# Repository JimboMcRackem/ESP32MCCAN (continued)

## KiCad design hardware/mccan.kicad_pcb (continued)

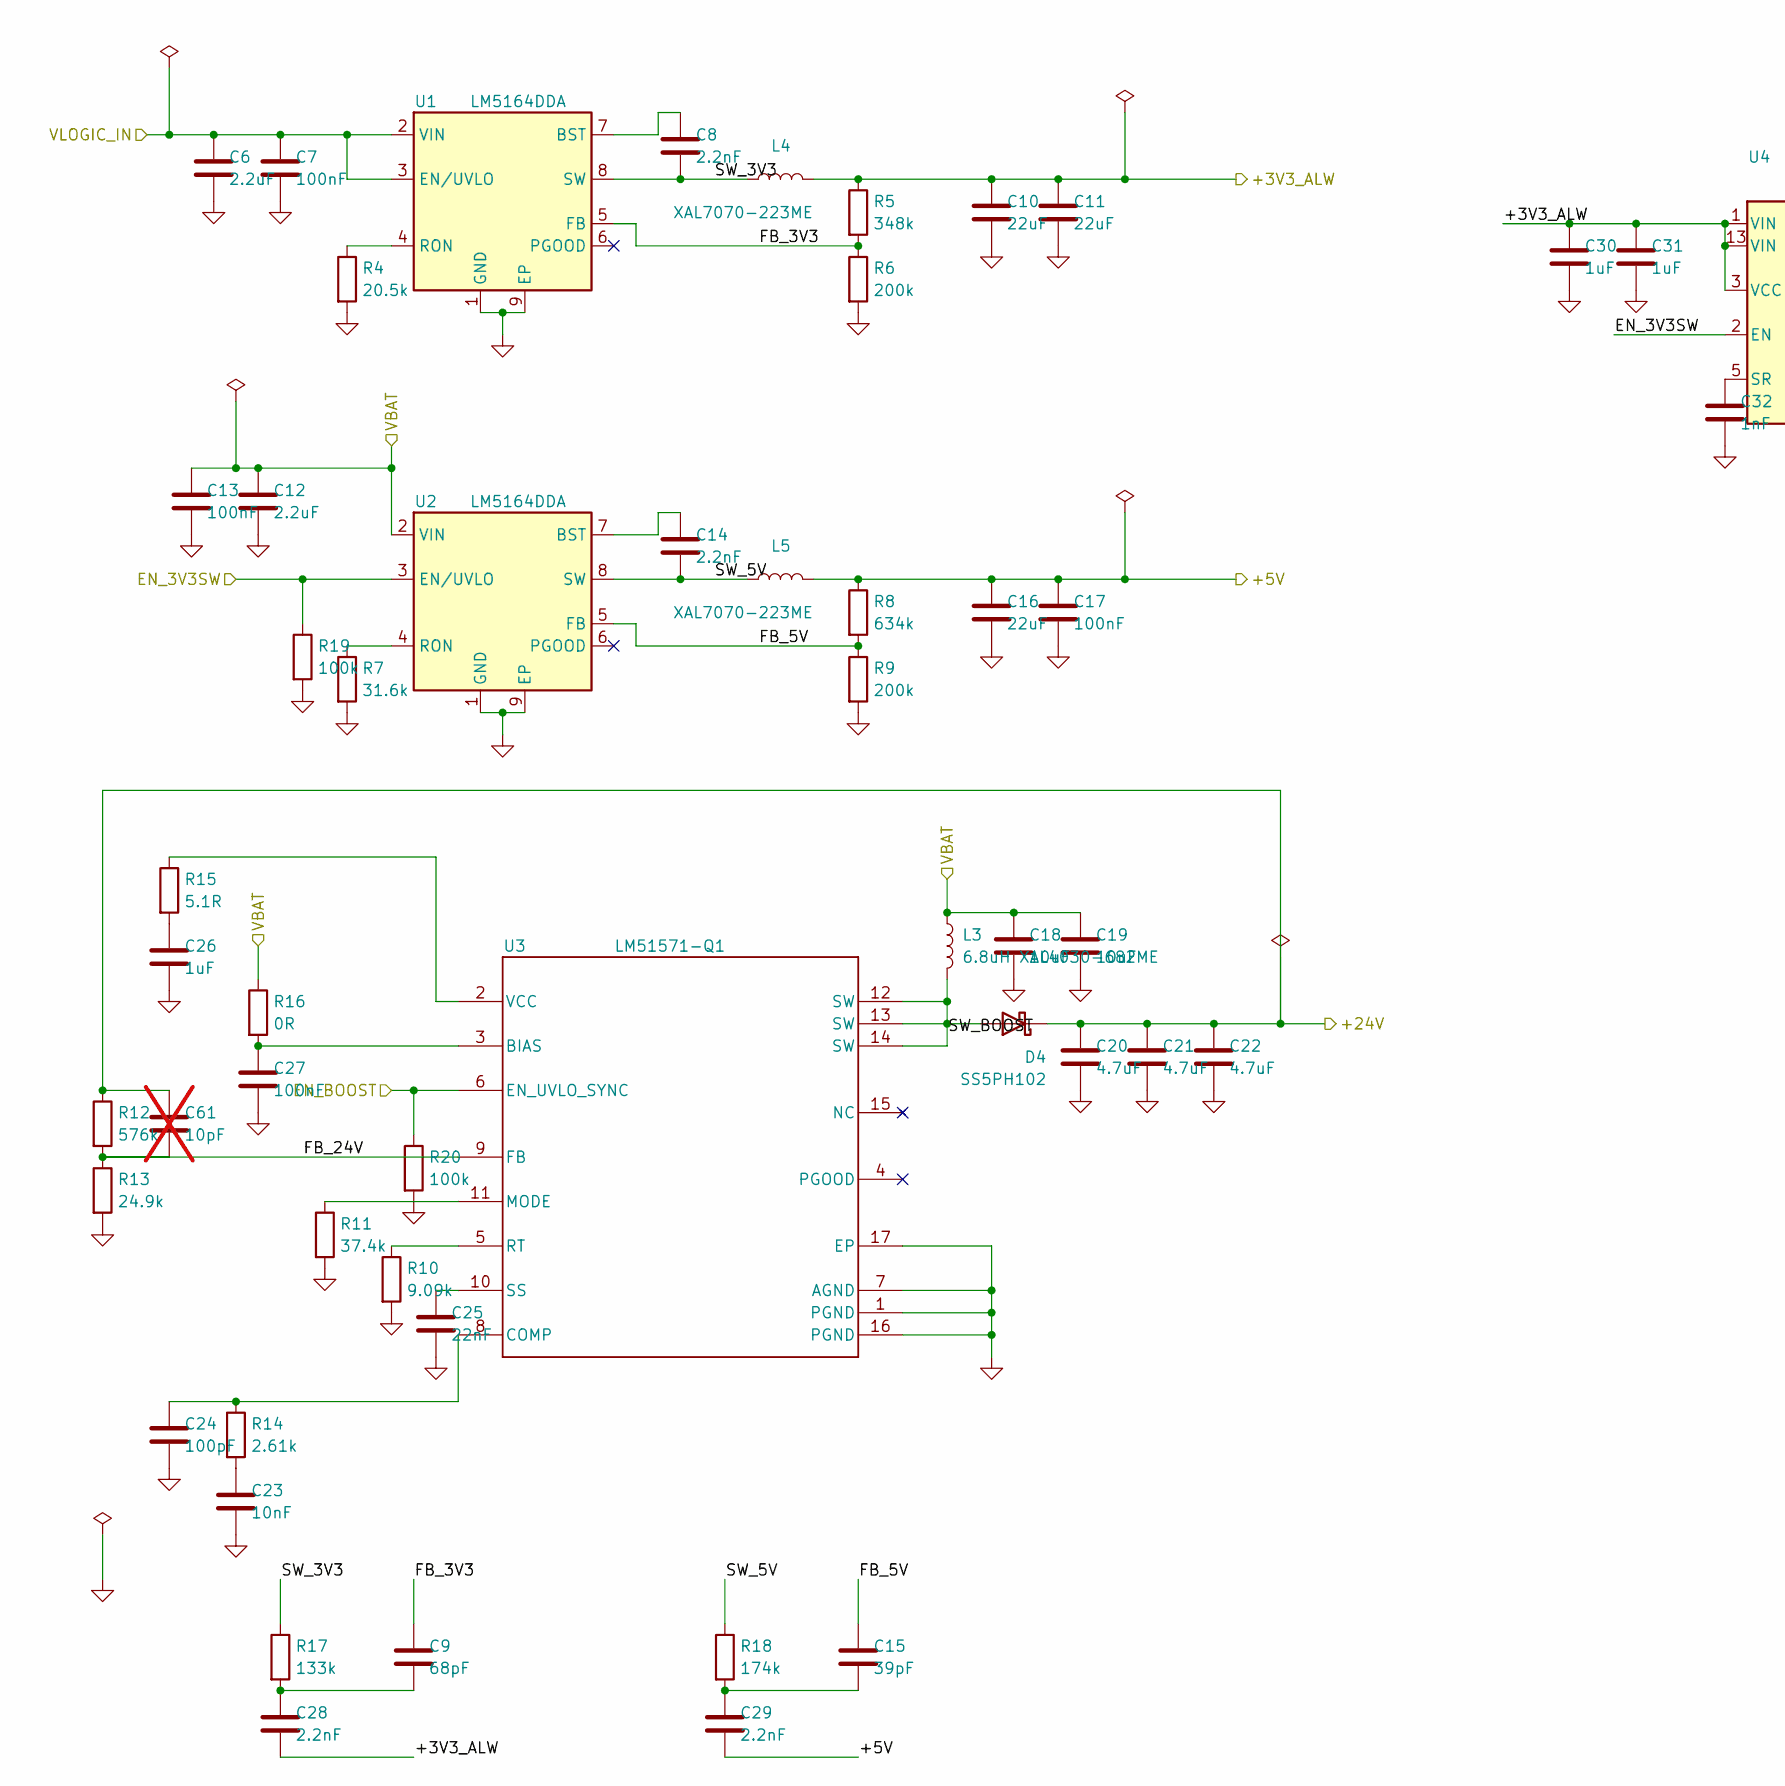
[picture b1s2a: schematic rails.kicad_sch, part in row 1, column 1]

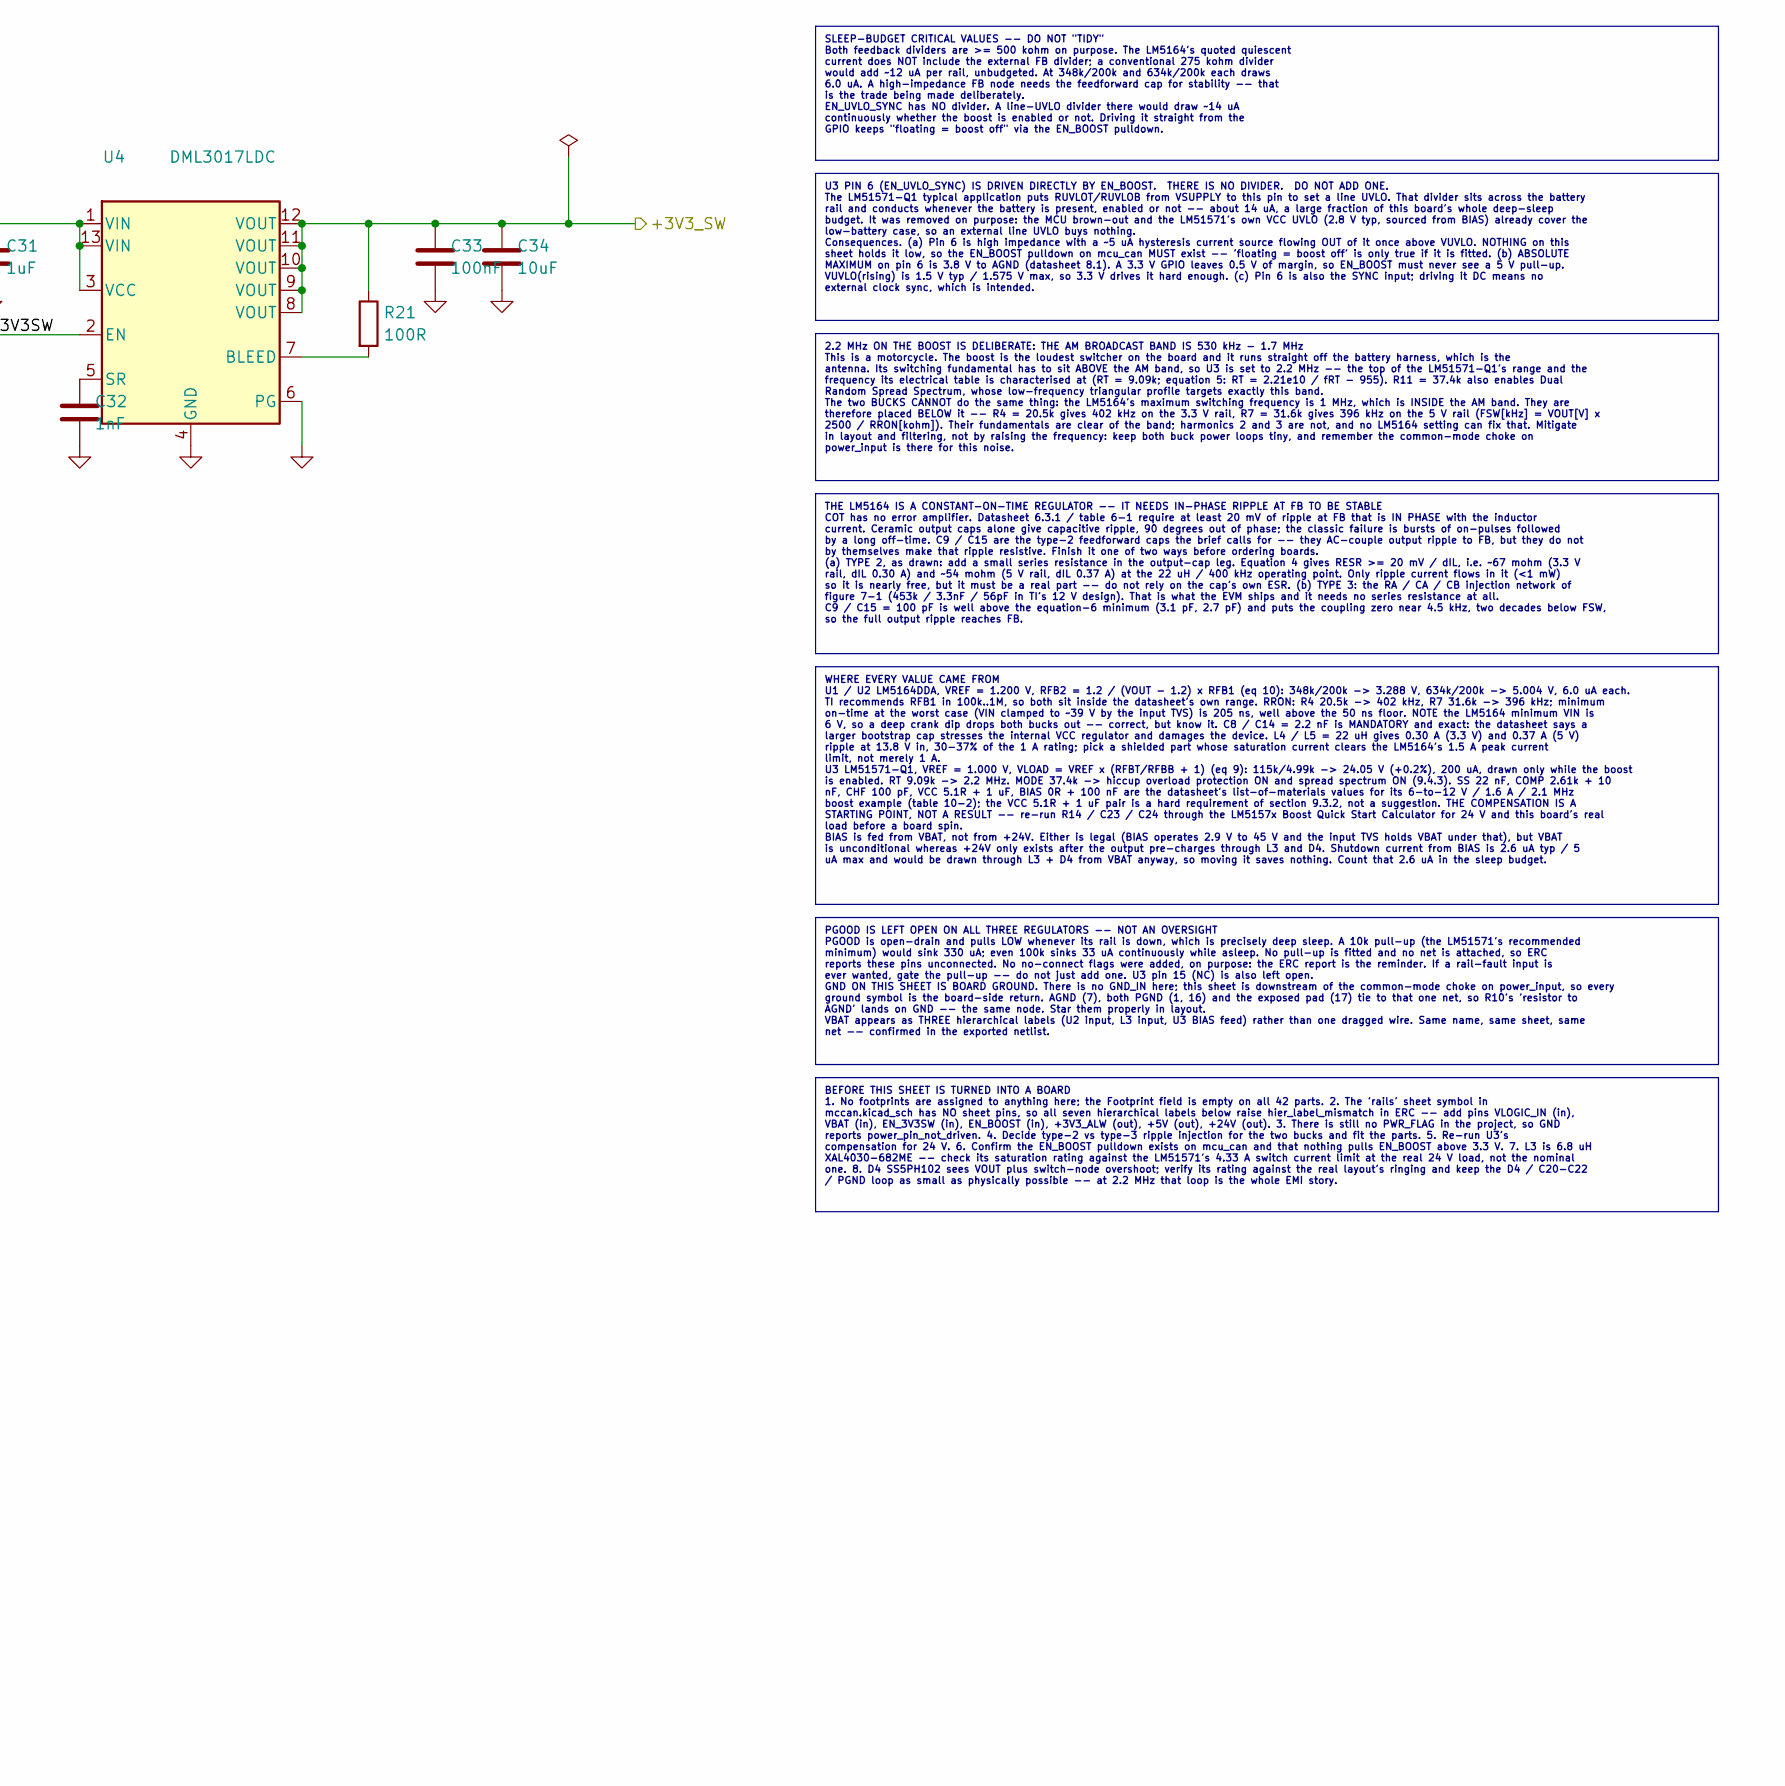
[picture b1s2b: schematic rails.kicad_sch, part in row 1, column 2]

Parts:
C6, C12: 2.2uF; C_1206_3216Metric
C7, C13: 100nF; C_0805_2012Metric
C8, C14, C28, C29: 2.2nF; C_0603_1608Metric
C9: 68pF; C_0603_1608Metric
C10, C11, C16: 22uF; C_0603_1608Metric
C15: 39pF; C_0603_1608Metric
C17, C27, C33: 100nF; C_0603_1608Metric
C18, C19: 10uF; C_1210_3225Metric
C20, C21, C22: 4.7uF; C_1206_3216Metric
C23: 10nF; C_0603_1608Metric
C24: 100pF; C_0603_1608Metric
C25: 22nF; C_0603_1608Metric
C26, C30, C31: 1uF; C_0603_1608Metric
C32: 1nF; C_0603_1608Metric
C34: 10uF; C_0603_1608Metric
C61: 10pF; C_0603_1608Metric; not fitted
D4: SS5PH102; TO-277A
L3: 6.8uH XAL4030-682ME; L_Coilcraft_XAL4030-XXX
L4, L5: XAL7070-223ME; L_Coilcraft_XAL7070-XXX
R4: 20.5k; R_0603_1608Metric
R5: 348k; R_0603_1608Metric
R6, R9: 200k; R_0603_1608Metric
R7: 31.6k; R_0603_1608Metric
R8: 634k; R_0603_1608Metric
R10: 9.09k; R_0603_1608Metric
R11: 37.4k; R_0603_1608Metric
R12: 576k; R_0603_1608Metric
R13: 24.9k; R_0603_1608Metric
R14: 2.61k; R_0603_1608Metric
R15: 5.1R; R_0603_1608Metric
R16: 0R; R_0603_1608Metric
R17: 133k; R_0603_1608Metric
R18: 174k; R_0603_1608Metric
R19, R20: 100k; R_0603_1608Metric
R21: 100R; R_0603_1608Metric
U1, U2: LM5164DDA; SOIC-8-1EP_3.9x4.9mm_P1.27mm_EP2.62x3.51mm
U3: LM51571-Q1; QFN-16-1EP_3x3mm_P0.5mm_EP1.675x1.675mm
U4: DML3017LDC; DFN-12-1EP_3x3mm_P0.5mm_EP2.05x2.86mm

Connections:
/+3V3_ALW: C10.1, C11.1, C28.2, C30.1, C31.1, L4.2, R5.1, U4.1 (VIN), U4.3 (VCC), U4.13 (VIN); also elsewhere on the board
/+3V3_SW: C33.1, C34.1, R21.1, U4.8 (VOUT), U4.9 (VOUT), U4.10 (VOUT), U4.11 (VOUT), U4.12 (VOUT); also elsewhere on the board
/+5V: C16.1, C17.1, C29.2, L5.2, R8.1; also elsewhere on the board
/+24V: C20.1, C21.1, C22.1, C61.1, D4.1 (K), D4.3 (K), R12.1; also elsewhere on the board
/EN_3V3SW: R19.1, U2.3 (EN/UVLO), U4.2 (EN); also elsewhere on the board
/EN_BOOST: R20.1, U3.6 (EN_UVLO_SYNC); also elsewhere on the board
/VBAT: C12.1, C13.1, C18.1, C19.1, L3.1, R16.1, U2.2 (VIN); also elsewhere on the board
/VLOGIC_IN: C6.1, C7.1, U1.2 (VIN), U1.3 (EN/UVLO); also elsewhere on the board
/rails/FB_3V3: C9.1, R5.2, R6.1, U1.5 (FB)
/rails/FB_5V: C15.1, R8.2, R9.1, U2.5 (FB)
/rails/FB_24V: C61.2, R12.2, R13.1, U3.9 (FB)
/rails/SW_3V3: C8.2, L4.1, R17.1, U1.8 (SW)
/rails/SW_5V: C14.2, L5.1, R18.1, U2.8 (SW)
/rails/SW_BOOST: D4.2 (A), L3.2, U3.12 (SW), U3.13 (SW), U3.14 (SW)
unnamed: C15.2, C29.1, R18.2
unnamed: C23.1, R14.2
unnamed: C26.1, R15.2
unnamed: C9.2, C28.1, R17.2
unnamed: C8.1, U1.7 (BST)
unnamed: R4.1, U1.4 (RON)
unnamed: C14.1, U2.7 (BST)
unnamed: R7.1, U2.4 (RON)
unnamed: C27.1, R16.2, U3.3 (BIAS)
unnamed: C24.1, R14.1, U3.8 (COMP)
unnamed: R10.1, U3.5 (RT)
unnamed: C25.1, U3.10 (SS)
unnamed: R15.1, U3.2 (VCC)
unnamed: R21.2, U4.7 (BLEED)
unnamed: C32.1, U4.5 (SR)

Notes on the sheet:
PGOOD IS LEFT OPEN ON ALL THREE REGULATORS -- NOT AN OVERSIGHT PGOOD is open-drain and pulls LOW whenever its rail is down, which is precisely deep sleep. A 10k pull-up (the LM51571's recommended minimum) would sink 330 uA; even 100k sinks 33 uA continuously while asleep. No pull-up is fitted and n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
2.2 MHz ON THE BOOST IS DELIBERATE: THE AM BROADCAST BAND IS 530 kHz - 1.7 MHz This is a motorcycle. The boost is the loudest switcher on the board and it runs straight off the battery harness, which is the antenna. Its switching fundamental has to sit ABOVE the AM band, so U3 is set to 2.2 MHz -- 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
BEFORE THIS SHEET IS TURNED INTO A BOARD 1. No footprints are assigned to anything here; the Footprint field is empty on all 42 parts. 2. The 'rails' sheet symbol in mccan.kicad_sch has NO sheet pins, so all seven hierarchical labels below raise hier_label_mismatch in ERC -- add pins VLOGIC_IN (in)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
WHERE EVERY VALUE CAME FROM U1 / U2 LM5164DDA, VREF = 1.200 V, RFB2 = 1.2 / (VOUT - 1.2) x RFB1 (eq 10): 348k/200k -> 3.288 V, 634k/200k -> 5.004 V, 6.0 uA each. TI recommends RFB1 in 100k..1M, so both sit inside the datasheet's own range. RRON: R4 20.5k -> 402 kHz, R7 31.6k -> 396 kHz; minimum on-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
THE LM5164 IS A CONSTANT-ON-TIME REGULATOR -- IT NEEDS IN-PHASE RIPPLE AT FB TO BE STABLE COT has no error amplifier. Datasheet 6.3.1 / table 6-1 require at least 20 mV of ripple at FB that is IN PHASE with the inductor current. Ceramic output caps alone give capacitive ripple, 90 degrees out of ph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
SLEEP-BUDGET CRITICAL VALUES -- DO NOT "TIDY" Both feedback dividers are >= 500 kohm on purpose. The LM5164's quoted quiescent current does NOT include the external FB divider; a conventional 275 kohm divider would add ~12 uA per rail, unbudgeted. At 348k/200k and 634k/200k each draws 6.0 uA. A hig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
U3 PIN 6 (EN_UVLO_SYNC) IS DRIVEN DIRECTLY BY EN_BOOST. THERE IS NO DIVIDER. DO NOT ADD ONE. The LM51571-Q1 typical application puts RUVLOT/RUVLOB from VSUPPLY to this pin to set a line UVLO. That divider sits across the battery rail and conducts whenever the battery is present, enabled or not -- a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

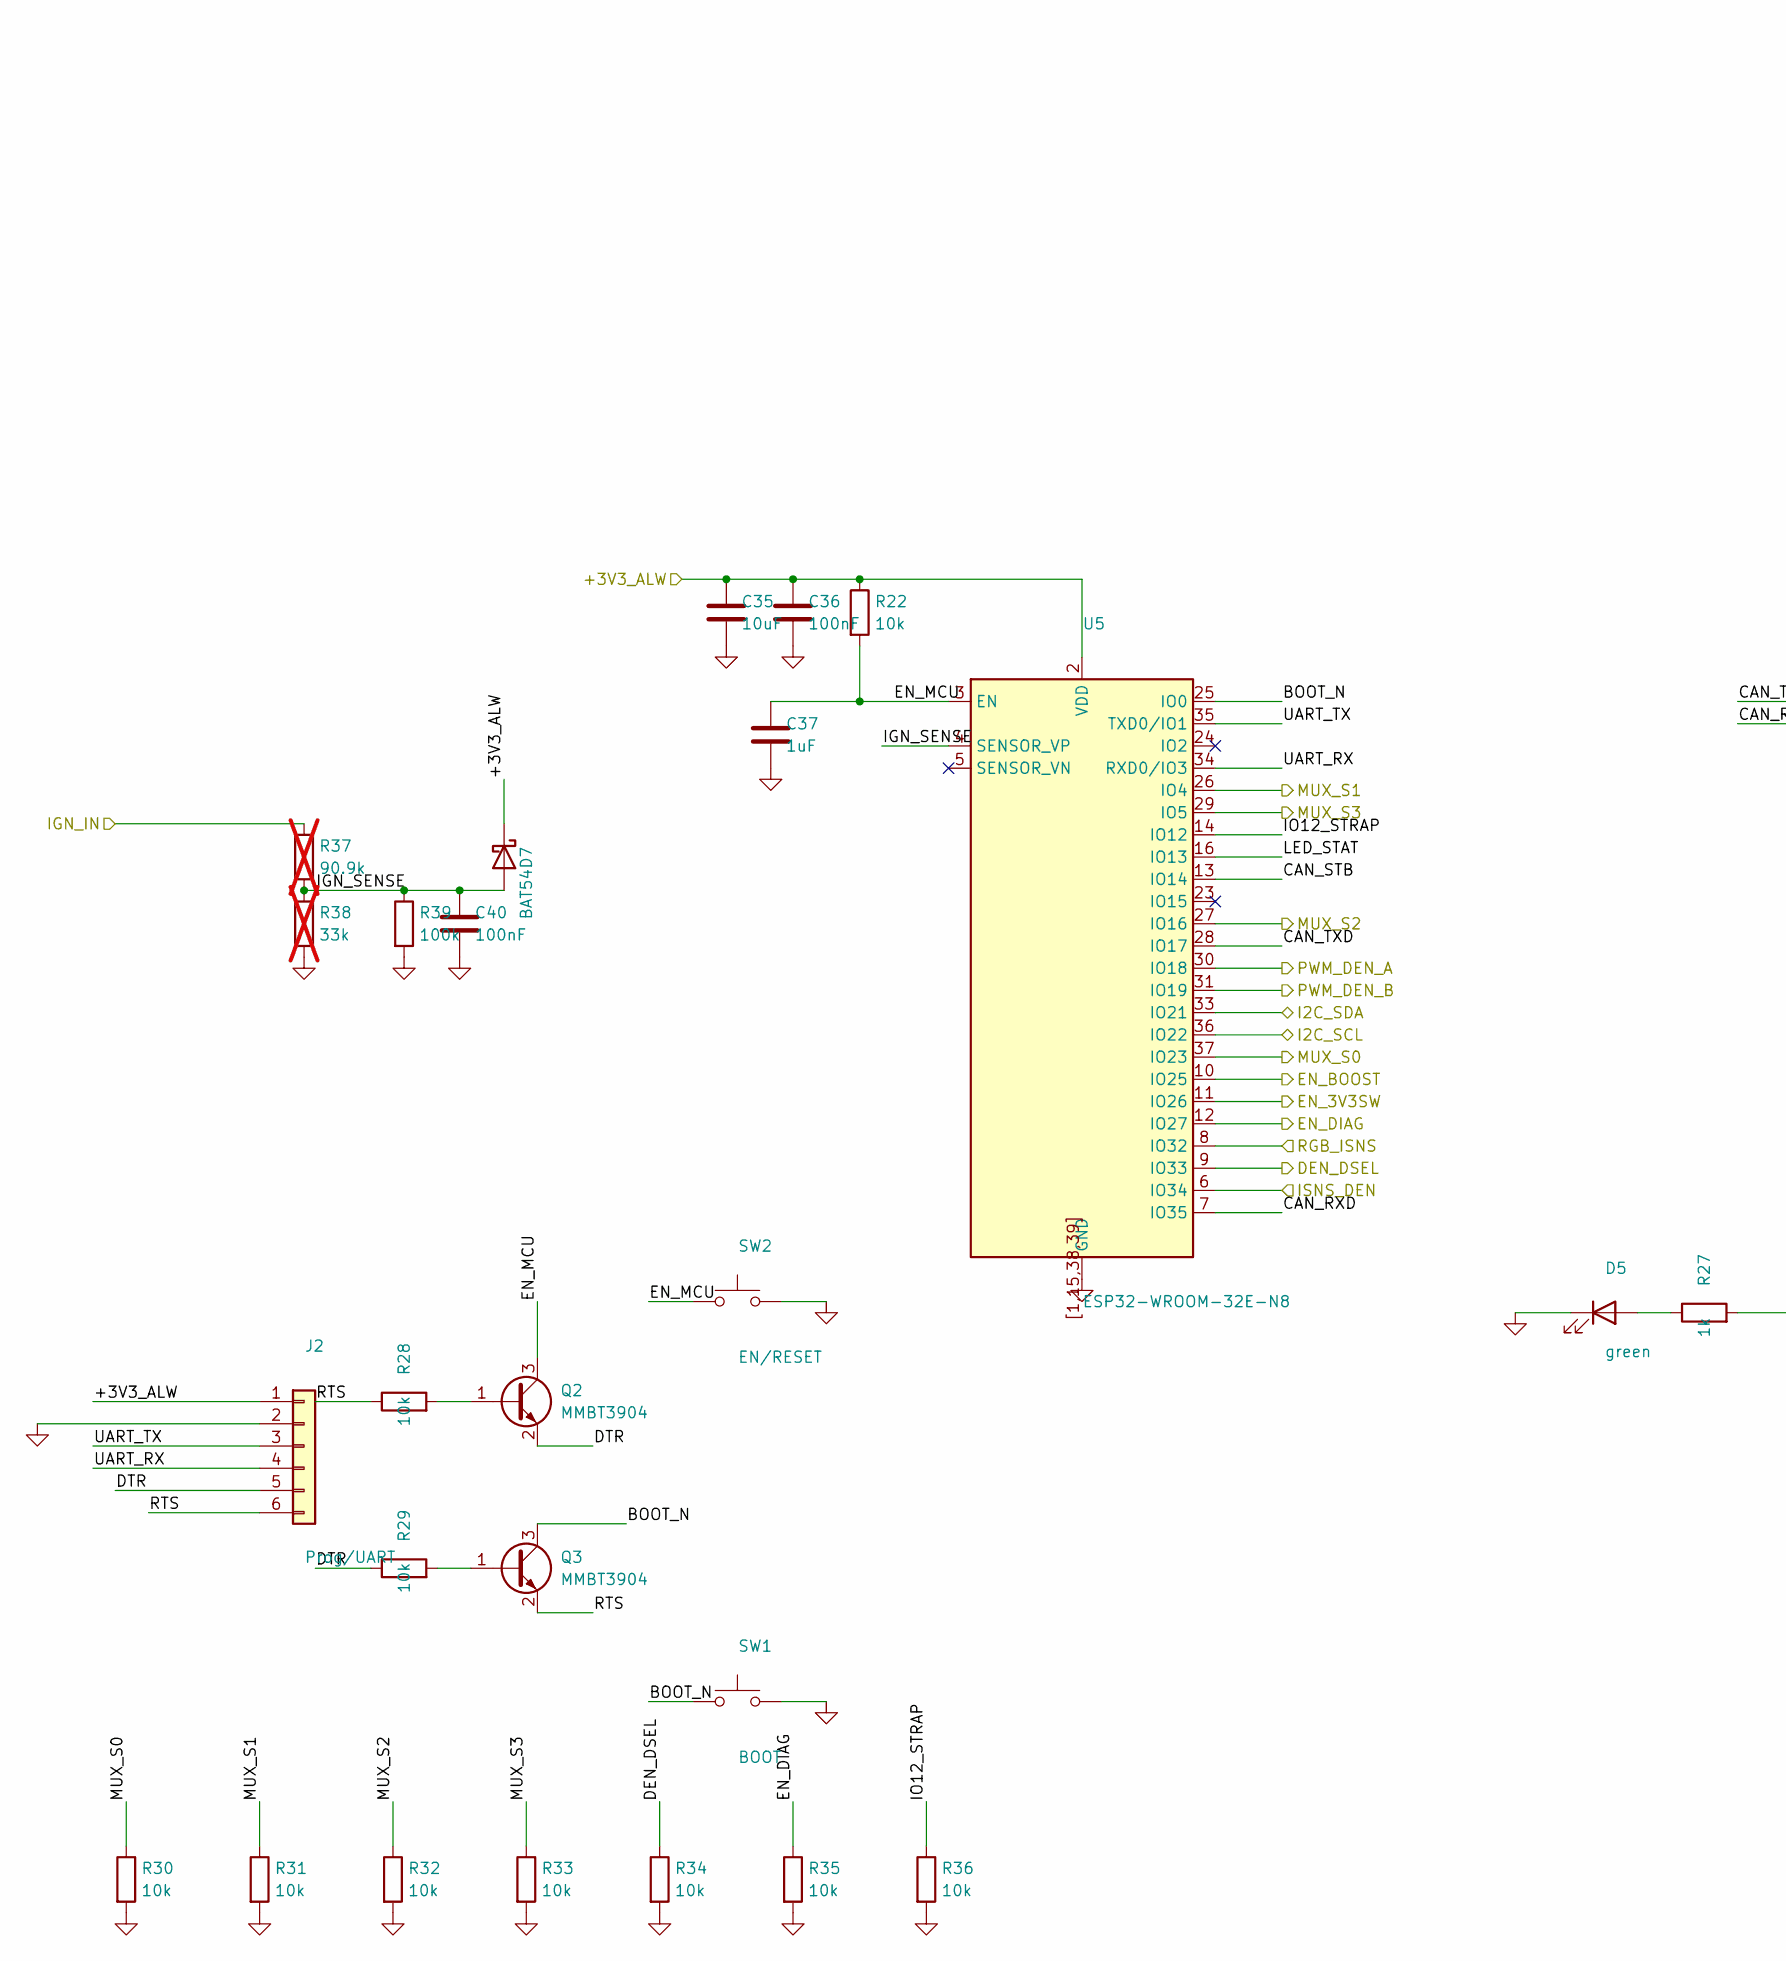
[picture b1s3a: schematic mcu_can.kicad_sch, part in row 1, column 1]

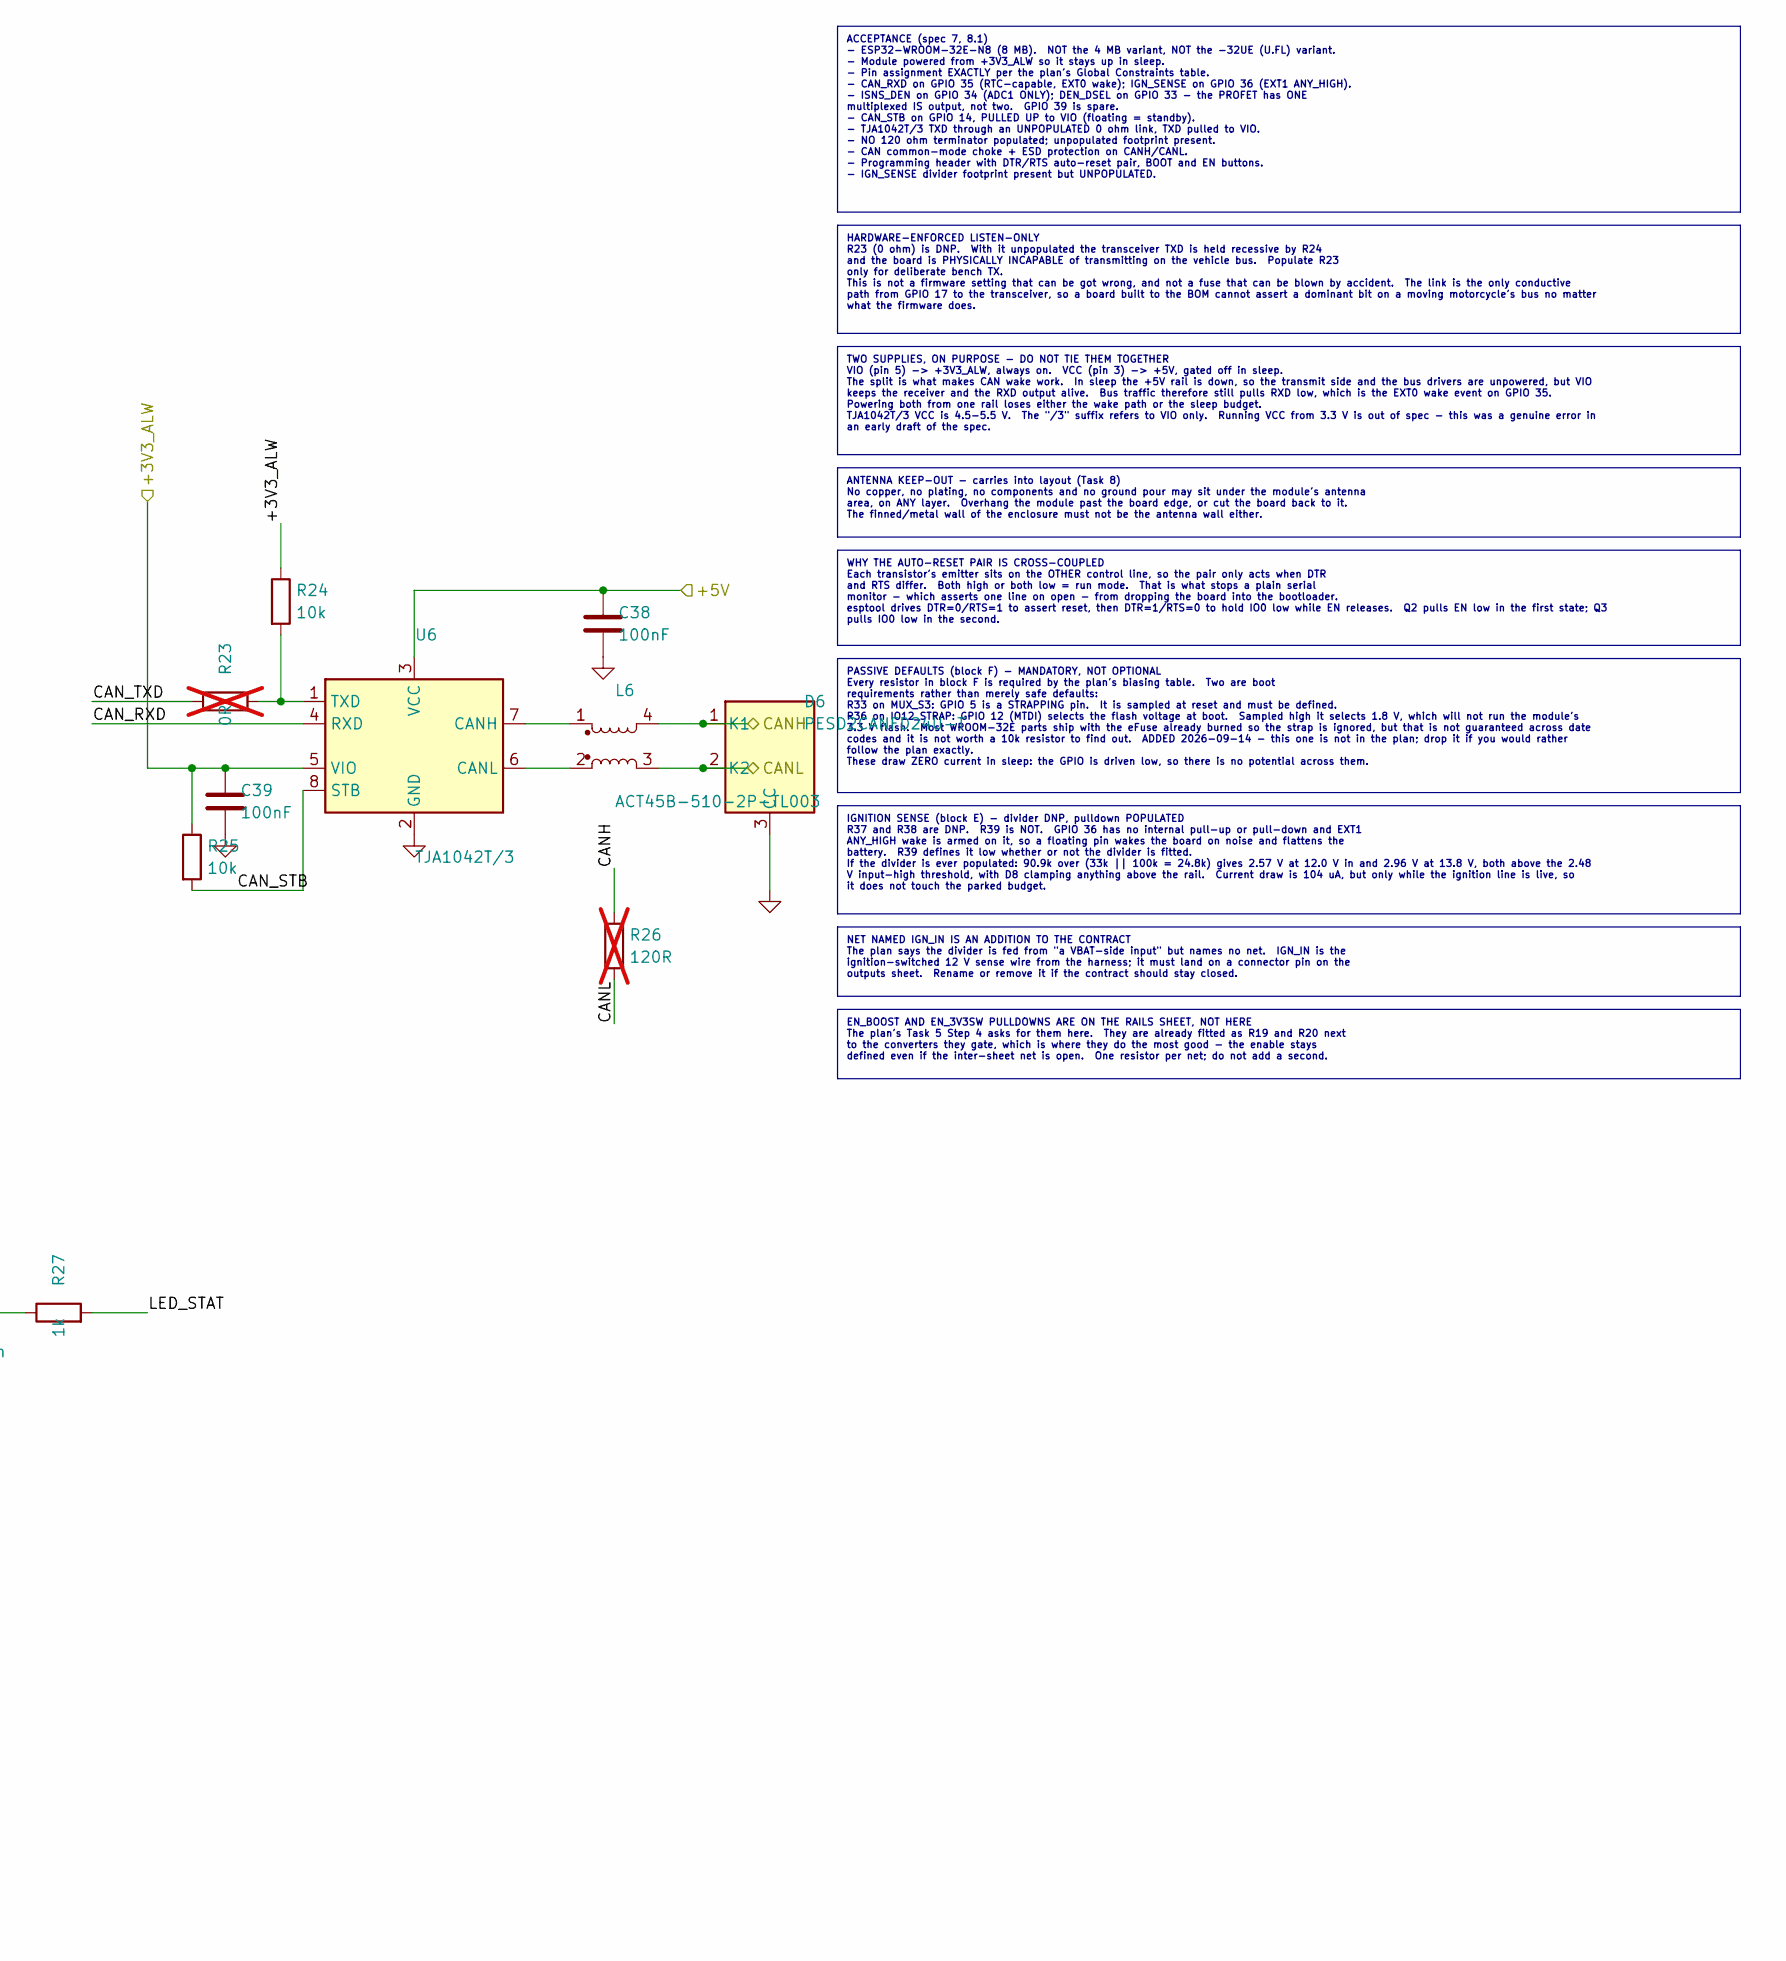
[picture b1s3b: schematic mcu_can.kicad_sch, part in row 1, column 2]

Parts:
C35: 10uF; C_0603_1608Metric
C36, C38, C39, C40: 100nF; C_0603_1608Metric
C37: 1uF; C_0603_1608Metric
D5: green; LED_0603_1608Metric
D6: PESD2CANFD24U-T; SOT-23
D7: BAT54; D_SOD-123
J2: Prog/UART; PinHeader_1x06_P2.54mm_Vertical
L6: ACT45B-510-2P-TL003; TDK_ACT45B
Q2, Q3: MMBT3904; SOT-23
R22, R24, R25, R28, R29, R30, R31, R32, R33, R34, R35, R36: 10k; R_0603_1608Metric
R23: 0R; R_0603_1608Metric; not fitted
R26: 120R; R_0603_1608Metric; not fitted
R27: 1k; R_0603_1608Metric
R37: 90.9k; R_0603_1608Metric; not fitted
R38: 33k; R_0603_1608Metric; not fitted
R39: 100k; R_0603_1608Metric
SW1: BOOT; Panasonic_EVQPUJ_EVQPUA
SW2: EN/RESET; Panasonic_EVQPUJ_EVQPUA
U5: ESP32-WROOM-32E-N8; ESP32-WROOM-32E
U6: TJA1042T/3; SOIC-8_3.9x4.9mm_P1.27mm

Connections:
/+3V3_ALW: C35.1, C36.1, C39.1, D7.1 (K), J2.1, R22.1, R24.1, R25.1, U5.2 (VDD), U6.5 (VIO); also elsewhere on the board
/+5V: C38.1, U6.3 (VCC); also elsewhere on the board
/CANH: D6.1 (K1), L6.4, R26.1; also elsewhere on the board
/CANL: D6.2 (K2), L6.3, R26.2; also elsewhere on the board
/DEN_DSEL: R34.1, U5.9 (IO33); also elsewhere on the board
/EN_3V3SW: U5.11 (IO26); also elsewhere on the board
/EN_BOOST: U5.10 (IO25); also elsewhere on the board
/EN_DIAG: R35.1, U5.12 (IO27); also elsewhere on the board
/I2C_SCL: U5.36 (IO22); also elsewhere on the board
/I2C_SDA: U5.33 (IO21); also elsewhere on the board
/IGN_IN: R37.1; also elsewhere on the board
/ISNS_DEN: U5.6 (IO34); also elsewhere on the board
/MUX_S0: R30.1, U5.37 (IO23); also elsewhere on the board
/MUX_S1: R31.1, U5.26 (IO4); also elsewhere on the board
/MUX_S2: R32.1, U5.27 (IO16); also elsewhere on the board
/MUX_S3: R33.1, U5.29 (IO5); also elsewhere on the board
/PWM_DEN_A: U5.30 (IO18); also elsewhere on the board
/PWM_DEN_B: U5.31 (IO19); also elsewhere on the board
/RGB_ISNS: U5.8 (IO32); also elsewhere on the board
/mcu_can/BOOT_N: Q3.3 (C), SW1.1, U5.25 (IO0)
/mcu_can/CAN_RXD: U5.7 (IO35), U6.4 (RXD)
/mcu_can/CAN_STB: R25.2, U5.13 (IO14), U6.8 (STB)
/mcu_can/CAN_TXD: R23.1, U5.28 (IO17)
/mcu_can/DTR: J2.5, Q2.2 (E), R29.1
/mcu_can/EN_MCU: C37.1, Q2.3 (C), R22.2, SW2.1, U5.3 (EN)
/mcu_can/IGN_SENSE: C40.1, D7.2 (A), R37.2, R38.1, R39.1, U5.4 (SENSOR_VP)
/mcu_can/IO12_STRAP: R36.1, U5.14 (IO12)
/mcu_can/LED_STAT: R27.2, U5.16 (IO13)
/mcu_can/RTS: J2.6, Q3.2 (E), R28.1
/mcu_can/UART_RX: J2.4, U5.34 (RXD0/IO3)
/mcu_can/UART_TX: J2.3, U5.35 (TXD0/IO1)
unnamed: D5.2 (A), R27.1
unnamed: Q2.1 (B), R28.2
unnamed: Q3.1 (B), R29.2
unnamed: L6.1, U6.7 (CANH)
unnamed: L6.2, U6.6 (CANL)
unnamed: R23.2, R24.2, U6.1 (TXD)

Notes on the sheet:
PASSIVE DEFAULTS (block F) - MANDATORY, NOT OPTIONAL Every resistor in block F is required by the plan's biasing table. Two are boot requirements rather than merely safe defaults: R33 on MUX_S3: GPIO 5 is a STRAPPING pin. It is sampled at reset and must be defined. R36 on IO12_STRAP: GPIO 12 (MTDI)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
NET NAMED IGN_IN IS AN ADDITION TO THE CONTRACT The plan says the divider is fed from "a VBAT-side input" but names no net. IGN_IN is the ignition-switched 12 V sense wire from the harness; it must land on a connector pin on the outputs sheet. Rename or remove it if the contract should stay closed.
TWO SUPPLIES, ON PURPOSE - DO NOT TIE THEM TOGETHER VIO (pin 5) -> +3V3_ALW, always on. VCC (pin 3) -> +5V, gated off in sleep. The split is what makes CAN wake work. In sleep the +5V rail is down, so the transmit side and the bus drivers are unpowered, but VIO keeps the receiver and the RXD output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
IGNITION SENSE (block E) - divider DNP, pulldown POPULATED R37 and R38 are DNP. R39 is NOT. GPIO 36 has no internal pull-up or pull-down and EXT1 ANY_HIGH wake is armed on it, so a floating pin wakes the board on noise and flattens the battery. R39 defines it low whether or not the divider is fitte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
ANTENNA KEEP-OUT - carries into layout (Task 8) No copper, no plating, no components and no ground pour may sit under the module's antenna area, on ANY layer. Overhang the module past the board edge, or cut the board back to it. The finned/metal wall of the enclosure must not be the antenna wall ei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
EN_BOOST AND EN_3V3SW PULLDOWNS ARE ON THE RAILS SHEET, NOT HERE The plan's Task 5 Step 4 asks for them here. They are already fitted as R19 and R20 next to the converters they gate, which is where they do the most good - the enable stays defined even if the inter-sheet net is open. One resistor pe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
WHY THE AUTO-RESET PAIR IS CROSS-COUPLED Each transistor's emitter sits on the OTHER control line, so the pair only acts when DTR and RTS differ. Both high or both low = run mode. That is what stops a plain serial monitor - which asserts one line on open - from dropping the board into the bootloade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
ACCEPTANCE (spec 7, 8.1) - ESP32-WROOM-32E-N8 (8 MB). NOT the 4 MB variant, NOT the -32UE (U.FL) variant. - Module powered from +3V3_ALW so it stays up in sleep. - Pin assignment EXACTLY per the plan's Global Constraints table. - CAN_RXD on GPIO 35 (RTC-capable, EXT0 wake); IGN_SENSE on GPIO 36 (EX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
HARDWARE-ENFORCED LISTEN-ONLY R23 (0 ohm) is DNP. With it unpopulated the transceiver TXD is held recessive by R24 and the board is PHYSICALLY INCAPABLE of transmitting on the vehicle bus. Populate R23 only for deliberate bench TX. This is not a firmware setting that can be got wrong, and not a fus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
